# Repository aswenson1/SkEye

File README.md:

# SkEye
_Pronounced "Sky"_

CEN4907C Design Project (Formerly known as The Citadel)

## Introduction
SkEye is a tabletop interactive mapping system that uses AR/XR technology to track physical objects placed on a surface and dynamically projects or displays information around them, turning a table into a programmable spatial interface. SkEye allows users to upload their own scenarios, step through them, and replay past actions on the board.

## Architectural Elements
### External Interface
SkEye can output a window to a computer screen showing the camera output, perform a calibration routine, and track an object, outputting the objects coordinates and current location onto the screen. To connect to the persistent state, the current functionality of SkEye's software allows for recording and playback of object tracking sequences.

### Persistent State
SkEye allows users to save and play back replays of previous actions occurring on the tabletop. To record, a user can press `s` and move the object around. When finished, pressing `s` saves the recording, which can be replayed, allowing the user to see the location of tokens during the recorded period of time on the displayed graph. This functionality saves playbacks to a persistent JSON file which can be loaded later to play the recording again.

### Internal Systems

SkEye makes use of the OpenCV library to process images. For example, SkEye uses a script to generate ArUco markers (for corner detection) and detect these markers to determine the bounds of the board. Additionally, SkEye uses numpy and OpenCV modules to normalize the detected board into a coordinate plane, running camera pixels through a matrix to convert from px to coordinates, and an inverse matrix to do the opposite operation.

Currently, we are using the OpenCV Python library, but if problems arise with performance when we scale down to a smaller CPU, we may pivot to using C++ to deal with performance constraints. However, Python was chosen for the time being as it made it easy to quickly stand up multiple features for our proof-of-concept.

## Information Handling
### Communication
We are able to communicate with the webcam via USB and plan to when we switch to using a headless (Raspberry Pi) setup. The different python scripts also output to the terminal / save to files, meaning that other parts of the system will eventually be able to access these streams and use the output for their operations. Furthermore, we are able to communicate with the program using certain keybinds (such as numbers 1-5 for changing color detection, and s to save a recording). This allows us to make the system interactive until we have our physical controller set up.

### Integrity and Resilience
The current calibration setup runs through a set of test cases. If any of these fail during the 60s calibration period without being corrected, the calibration fails and the program exits. These criteria, including camera steadiness, brightness, how close the camera is to the table, etc, all make sure that SkEye can operate under the best conditions. Our goal for the next milestone is to set up calibration that happens continuously, helping to notify users of any issues that may arise during use.

## Software Setup

To set up the software environment for running our code, follow the following steps:
- navigate to the software/ directory
- run `./setup.sh`
  - this will create the .venv/ directory from the dependencies in  `requirements.txt`
- run `source ./venv/bin/activate`

## References
**Pitch Link:** https://youtu.be/Z7oE
## Contributors

#### Hardware
- Sami Al-Jamal
- Anders Swenson

#### Software
- Anna Hudson
- Timothy Macias
- Jacob Oram

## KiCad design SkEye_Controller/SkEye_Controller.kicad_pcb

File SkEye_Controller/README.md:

# SkEye Controller PCB

KiCad source files for the SkEye physical I/O controller, built around a socketed Raspberry Pi Pico / Pico H. The board provides buttons, status LEDs, and a 3.3 V UART development header. Camera and projector connections are handled by the host computer.

This is a preliminary hardware design. Native KiCad ERC/DRC and hardware testing have not been completed.

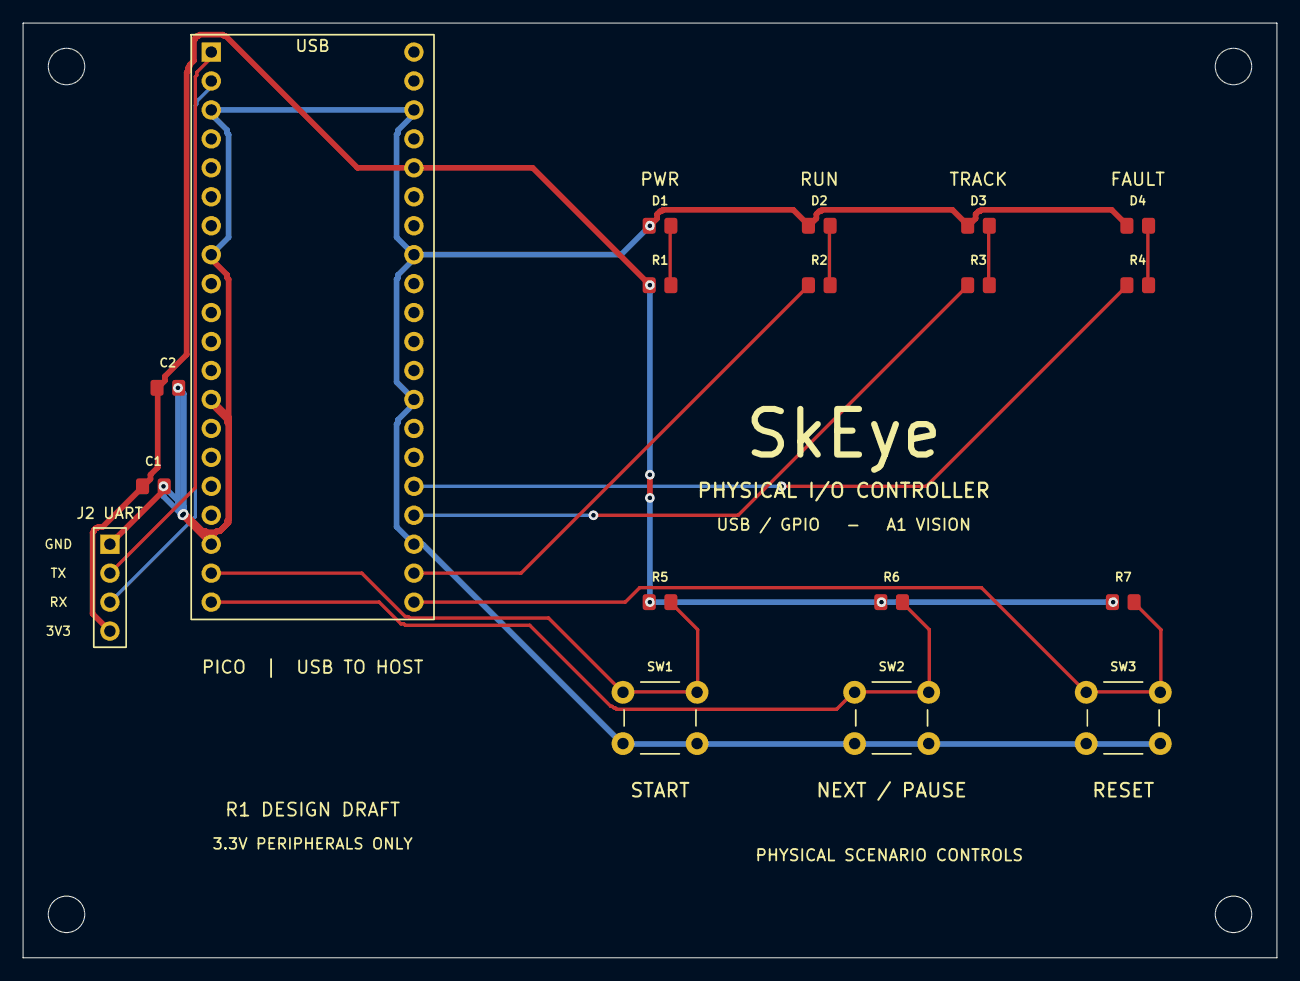
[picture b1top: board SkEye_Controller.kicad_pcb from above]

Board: 2 copper layers, 110.0 x 82.0 mm, 22 parts (0 on the bottom side), 14 nets.

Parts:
C1: 10uF / 10V X7R; C_0805
C2: 100nF / 10V X7R; C_0805
D1: PWR; LED_0805_Green
D2: RUN; LED_0805_Green
D3: TRACK; LED_0805_Amber
D4: FAULT; LED_0805_Red
H1, H2, H3, H4: M3 clearance 3.2mm; MountingHole_M3
J2: UART 3V3 logic; Header_1x04
R1, R2, R3, R4: 1k; R_0805
R5, R6, R7: 10k; R_0805
SW1, SW2, SW3: NO tactile 6mm; SW_PUSH_6mm
U1: Raspberry Pi Pico / Pico H; Pico_40_Socketed

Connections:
+3V3: C1.1, C2.1, J2.4, R1.1, R5.1, R6.1, R7.1, U1.36
BTN_PAUSE_N: R6.2, SW2.1, U1.20
BTN_RESET_N: R7.2, SW3.1, U1.21
BTN_START_N: R5.2, SW1.1, U1.19
GND: C1.2, C2.2, D1.1, D2.1, D3.1, D4.1, J2.1, SW1.2, SW2.2, SW3.2, U1.3, U1.8, U1.13, U1.18, U1.23, U1.28, U1.33, U1.38
LED_FAULT: R4.1, U1.25
LED_FAULT_A: D4.2, R4.2
LED_PWR_A: D1.2, R1.2
LED_RUN: R2.1, U1.22
LED_RUN_A: D2.2, R2.2
LED_TRACK: R3.1, U1.24
LED_TRACK_A: D3.2, R3.2
UART_RX: J2.3, U1.2
UART_TX: J2.2, U1.1
